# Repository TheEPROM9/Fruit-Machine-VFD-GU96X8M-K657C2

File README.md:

# Fruit-Machine-VFD-GU96X8M-K657C2
The GU96X8M-K657C2 is part of the GU96X8M series of VFD displays used in gambling machines, often deployed in pubs here in the UK.

Website Overview & Description: https://www.theeprom9.co.uk/electronics/projects-such/fruit-machine-vfd

My partner has worked on code to convert these to running on an ESP32 but has not published it yet, that one is up to him.

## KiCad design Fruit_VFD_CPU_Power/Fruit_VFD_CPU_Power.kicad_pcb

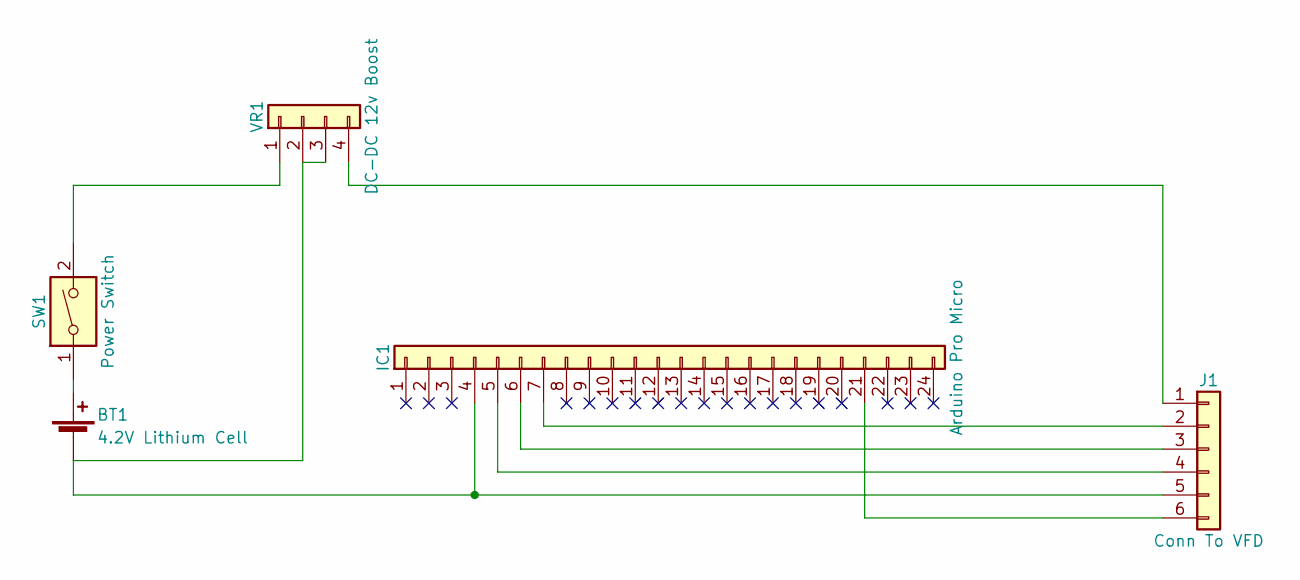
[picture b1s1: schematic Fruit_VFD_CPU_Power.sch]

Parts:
BT1: 4.2V Lithium Cell; Keystone_1042_1x18650
IC1: Arduino Pro Micro; DIP-24_W15.24mm_Socket_LongPads
J1: Conn To VFD; Socket_Strip_Straight_1x06_Pitch2.54mm
SW1: Power Switch; SW_CuK_OS102011MA1QN1_SPDT_Angled
VR1: DC-DC 12v Boost; Socket_Strip_Straight_1x04_Pitch2.54mm

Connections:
unnamed: BT1.1 (+), SW1.1
unnamed: BT1.2 (-), IC1.4, J1.5, VR1.2, VR1.3
unnamed: IC1.5, J1.4
unnamed: IC1.6, J1.3
unnamed: IC1.7, J1.2
unnamed: IC1.21, J1.6
unnamed: J1.1, VR1.4
unnamed: SW1.2, VR1.1

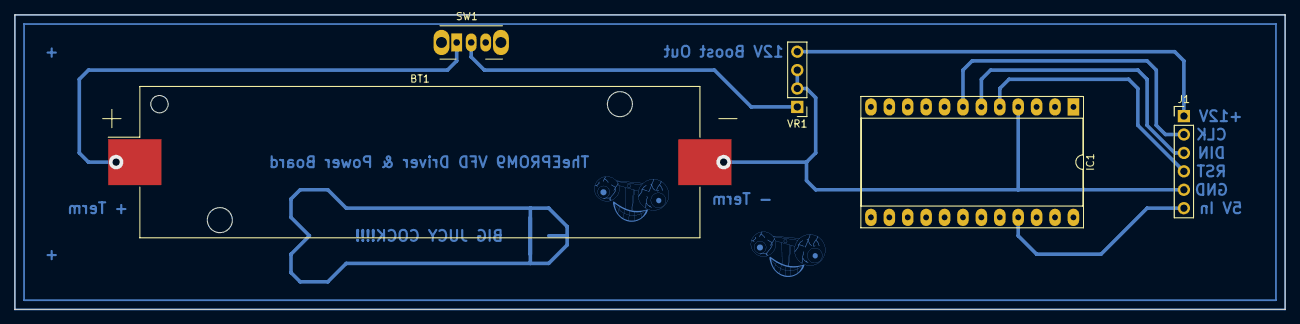
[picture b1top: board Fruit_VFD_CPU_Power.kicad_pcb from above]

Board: 2 copper layers, 175.3 x 40.6 mm, 5 parts (0 on the bottom side), 8 nets.
